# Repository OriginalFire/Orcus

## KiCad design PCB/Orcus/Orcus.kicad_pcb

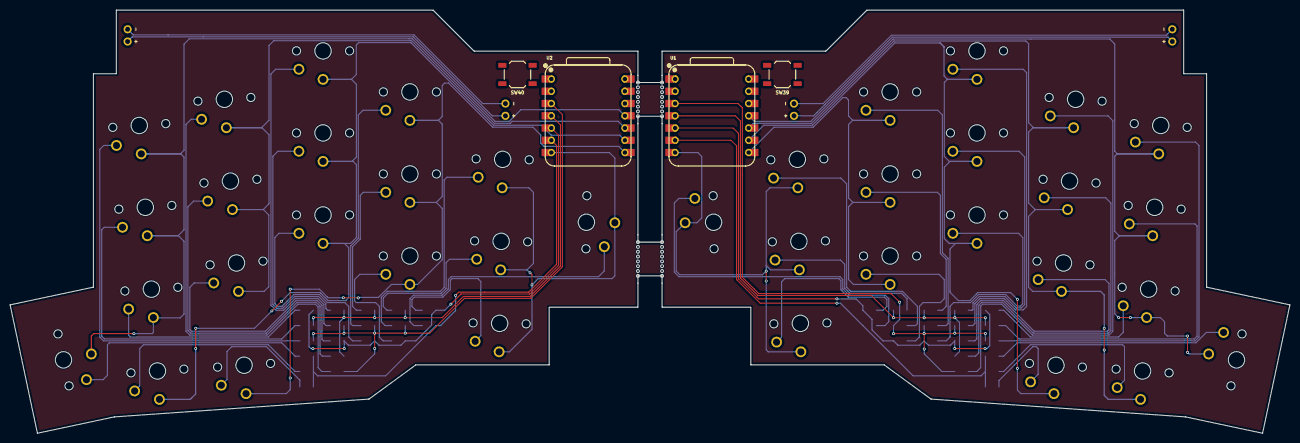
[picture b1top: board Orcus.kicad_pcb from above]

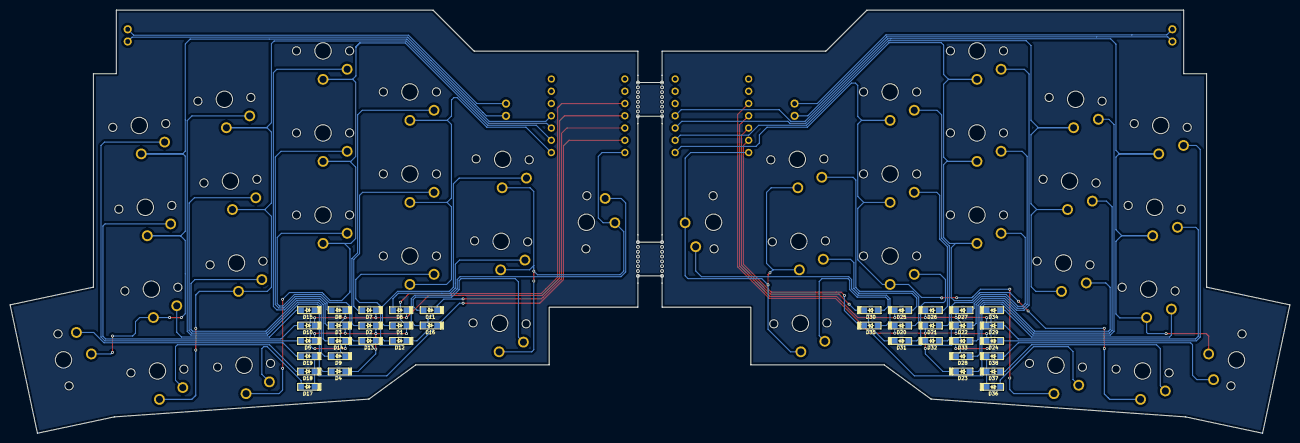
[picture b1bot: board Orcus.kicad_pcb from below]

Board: 2 copper layers, 265.2 x 87.7 mm, 86 parts (38 on the bottom side), 60 nets.

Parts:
D1, D2, D3, D4, D5, D6, D7, D8, D9, D10, D11, D12, D13, D14, D15, D16, D17, D18, D19, D20, D21, D22, D23, D24, D25, D26, D27, D28, D29, D30, D31, D32, D33, D34, D35, D36, D37, D38: D; D_SOD123F
SW1, SW2, SW3, SW4, SW5, SW6, SW7, SW8, SW9, SW10, SW11, SW12, SW13, SW14, SW15, SW16, SW17, SW18, SW19, SW20, SW21, SW22, SW23, SW24, SW25, SW26, SW27, SW28, SW29, SW30, SW31, SW32, SW33, SW34, SW35, SW36, SW37, SW38: MX_LED; Kailh-PG1350-1u-NoLED
SW39, SW40: RESET; SW_SPST_TL3342
SW41, SW42, SW43, SW44: BATT; Reset_Breakout
U1, U2: XIAO-nRF52840-DIP
mouse-bite-5mm-slot, mouse-bite-5mm-slot#2: VAL**; mouse-bite-5mm-slot-jlc

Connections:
L-col0: SW1.1, SW6.1, SW11.1, SW16.1, U1.7 (PB08_A6_D6_TX)
L-col1: SW2.1, SW7.1, SW12.1, U1.8 (PB09_A7_D7_RX)
L-col2: SW3.1, SW8.1, SW13.1, SW17.1, U1.9 (PA7_A8_D8_SCK)
L-col3: SW4.1, SW9.1, SW14.1, SW18.1, U1.10 (PA5_A9_D9_MISO)
L-col4: SW5.1, SW10.1, SW15.1, SW19.1, U1.11 (PA6_A10_D10_MOSI)
L-row0: D1.1 (K), D2.1 (K), D3.1 (K), D4.1 (K), D5.1 (K), U1.3 (PA10_A2_D2)
L-row1: D6.1 (K), D7.1 (K), D8.1 (K), D9.1 (K), D10.1 (K), U1.4 (PA11_A3_D3)
L-row2: D11.1 (K), D12.1 (K), D13.1 (K), D14.1 (K), D15.1 (K), U1.5 (PA8_A4_D4_SDA)
L-row3: D16.1 (K), D17.1 (K), D18.1 (K), D19.1 (K), U1.6 (PA9_A5_D5_SCL)
unnamed: D1.2 (A), SW1.2
unnamed: D2.2 (A), SW2.2
unnamed: D3.2 (A), SW3.2
unnamed: D4.2 (A), SW4.2
unnamed: D5.2 (A), SW5.2
unnamed: D6.2 (A), SW6.2
unnamed: D7.2 (A), SW7.2
unnamed: D8.2 (A), SW8.2
unnamed: D9.2 (A), SW9.2
unnamed: D10.2 (A), SW10.2
unnamed: D11.2 (A), SW11.2
unnamed: D12.2 (A), SW12.2
unnamed: D13.2 (A), SW13.2
unnamed: D14.2 (A), SW14.2
unnamed: D15.2 (A), SW15.2
unnamed: D16.2 (A), SW16.2
unnamed: D17.2 (A), SW17.2
unnamed: D18.2 (A), SW18.2
unnamed: D19.2 (A), SW19.2
unnamed: D20.2 (A), SW20.2
unnamed: D21.2 (A), SW21.2
unnamed: D22.2 (A), SW22.2
unnamed: D23.2 (A), SW23.2
unnamed: D24.2 (A), SW24.2
unnamed: D25.2 (A), SW25.2
unnamed: D26.2 (A), SW26.2
unnamed: D27.2 (A), SW27.2
unnamed: D28.2 (A), SW28.2
unnamed: D29.2 (A), SW29.2
unnamed: D30.2 (A), SW30.2
unnamed: D31.2 (A), SW31.2
unnamed: D32.2 (A), SW32.2
unnamed: D33.2 (A), SW33.2
unnamed: D34.2 (A), SW34.2
unnamed: D35.2 (A), SW35.2
unnamed: D36.2 (A), SW36.2
unnamed: D37.2 (A), SW37.2
unnamed: D38.2 (A), SW38.2
unnamed: SW41.1, SW42.1
unnamed: SW41.2, SW42.2
unnamed: SW43.1, SW44.1
unnamed: SW43.2, SW44.2
R-col0: SW20.1, SW25.1, SW30.1, SW35.1, U2.7 (PB08_A6_D6_TX)
R-col1: SW21.1, SW26.1, SW31.1, SW36.1, U2.8 (PB09_A7_D7_RX)
R-col2: SW22.1, SW27.1, SW32.1, SW37.1, U2.9 (PA7_A8_D8_SCK)
R-col3: SW23.1, SW28.1, SW33.1, U2.10 (PA5_A9_D9_MISO)
R-col4: SW24.1, SW29.1, SW34.1, SW38.1, U2.11 (PA6_A10_D10_MOSI)
R-row0: D20.1 (K), D21.1 (K), D22.1 (K), D23.1 (K), D24.1 (K), U2.3 (PA10_A2_D2)
R-row1: D25.1 (K), D26.1 (K), D27.1 (K), D28.1 (K), D29.1 (K), U2.4 (PA11_A3_D3)
R-row2: D30.1 (K), D31.1 (K), D32.1 (K), D33.1 (K), D34.1 (K), U2.5 (PA8_A4_D4_SDA)
R-row3: D35.1 (K), D36.1 (K), D37.1 (K), D38.1 (K), U2.6 (PA9_A5_D5_SCL)

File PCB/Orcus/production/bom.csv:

Designator,Footprint,Quantity,Value,LCSC Part #
"D1, D10, D11, D12, D13, D14, D15, D16, D17, D18, D19, D2, D20, D21, D22, D23, D24, D25, D26, D27, D28, D29, D3, D30, D31, D32, D33, D34, D35, D36, D37, D38, D4, D5, D6, D7, D8, D9",D_SOD123F,38,D,
"MOUSE-BITE-5MM-SLOT_2, MOUSE-BITE-5MM-SLOT",mouse-bite-5mm-slot-jlc,2,VAL**,
"SW1, SW10, SW11, SW12, SW13, SW14, SW15, SW16, SW17, SW18, SW19, SW2, SW20, SW21, SW22, SW23, SW24, SW25, SW26, SW27, SW28, SW29, SW3, SW30, SW31, SW32, SW33, SW34, SW35, SW36, SW37, SW38, SW4, SW5, SW6, SW7, SW8, SW9",Kailh-PG1350-1u-NoLED,38,MX_LED,
"SW39, SW40",SW_SPST_TL3342,2,RESET,
"SW41, SW42, SW43, SW44",Reset_Breakout,4,BATT,
"U1, U2",XIAO-nRF52840-DIP,2,XIAO-nRF52840-DIP,

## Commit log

2025-06-09 update sch
2025-06-23 footprint laid out
2025-06-23 update footprint, remove traces
2025-06-24 traces remaining
2025-06-24 almost final
2025-06-24 Gerber update
    Added Vscore
2025-06-24 replaced pad
2025-07-04 updated pcb and sch
2025-07-07 update pcb
2025-07-18 new sch
2025-07-18 updated pcb
2025-07-20 pcb update
2025-07-20 sch update
